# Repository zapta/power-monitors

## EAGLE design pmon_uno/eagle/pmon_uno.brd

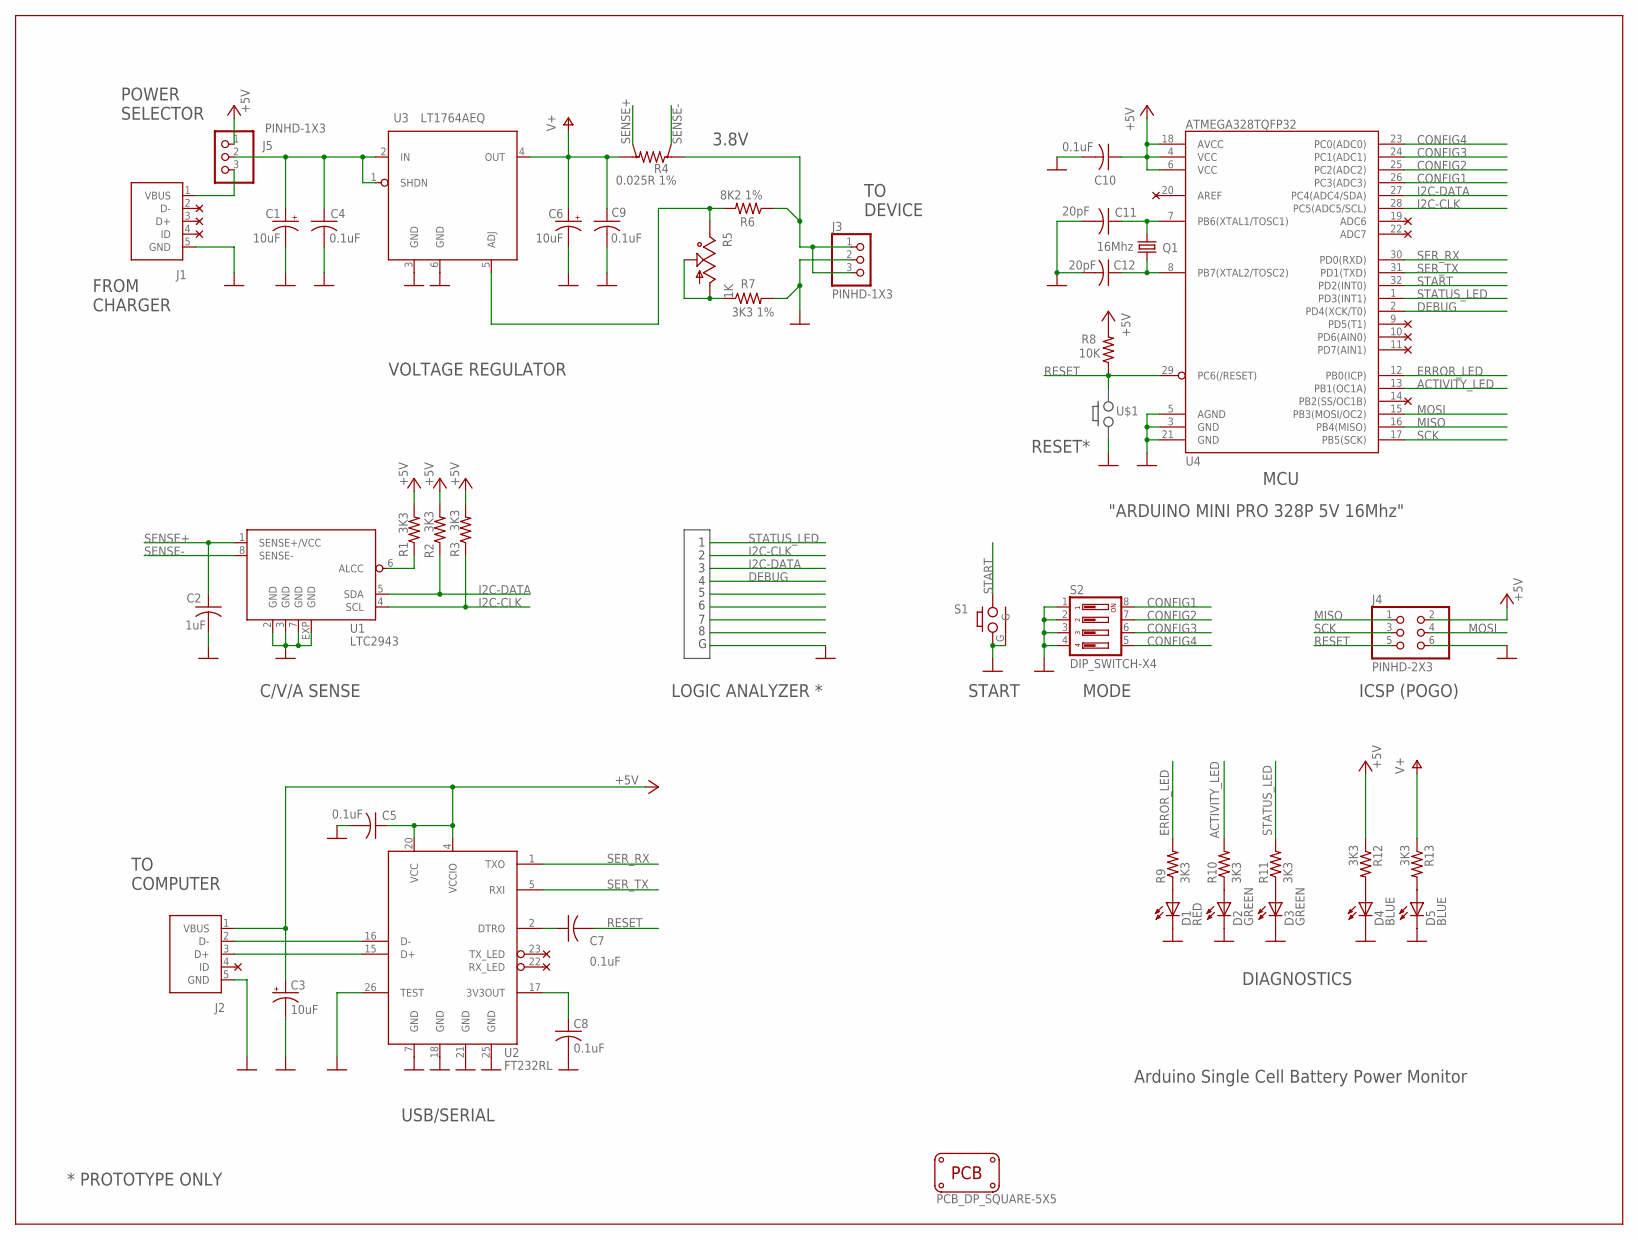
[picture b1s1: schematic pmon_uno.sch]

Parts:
C1, C3, C6: 10uF; A/3216-18R
C2: 1uF; C0603
C4, C5, C7, C8, C9, C10: 0.1uF; C0603
C11, C12: 20pF; C0603
D1: RED; 1206-LED
D2, D3: GREEN; 1206-LED
D4, D5: BLUE; 1206-LED
J1, J2: USB; USB-MICRO-ZX62RD-AB-5P8
J3, J5: PINHD-1X3; 1X03
J4: PINHD-2X3; 2X03
PCB1: PCB_DP_SQUARE-5X5; DP5050_V1
Q1: 16Mhz; CRYSTAL-CTS406
R1, R2, R3, R9, R10, R11, R12, R13: 3K3; R0603
R4: 0.025R 1%; KELVIN-6432
R5: 1K; TRIM-POT_SM-42/43A
R6: 8K2 1%; R0603
R7: 3K3 1%; R0603
R8: 10K; R0603
S1: PUSH_BUTTON_SHIELDED; TLE1105
S2: DIP_SWITCH-X4; DIP-SWITCH-X4
U1: LTC2943; DFN8-3X3
U2: FT232RL; SSOP28DB
U3: LT1764AEQ; TO263-5
U4: ATMEGA328TQFP32; TQFP32-08

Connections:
+5V: C3.+, C5.1, C10.1, J2.1 (VBUS), J4.2, J5.1, R1.2, R2.2, R3.2, R8.2, R12.1, U2.4 (VCCIO), U2.20 (VCC), U4.4 (VCC), U4.6 (VCC), U4.18 (AVCC)
ACTIVITY_LED: R10.2, U4.13 (PB1(OC1A))
CONFIG1: S2.8, U4.26 (PC3(ADC3))
CONFIG2: S2.7, U4.25 (PC2(ADC2))
CONFIG3: S2.6, U4.24 (PC1(ADC1))
CONFIG4: S2.5, U4.23 (PC0(ADC0))
DEBUG: U4.2 (PD4(XCK/T0))
ERROR_LED: R9.2, U4.12 (PB0(ICP))
GND: C1.-, C2.2, C3.-, C4.2, C5.2, C6.-, C8.2, C9.2, C10.2, C11.2, C12.2, D1.C, D2.C, D3.C, D4.C, D5.C, J1.5 (GND), J2.5 (GND), J3.2, J4.6, R7.2, S1.A (1), S1.G, S2.1, S2.2, S2.3, S2.4, U1.2 (GND), U1.3 (GND), U1.7 (GND), U1.EXP (GND), U2.7 (GND), U2.18 (GND), U2.21 (GND), U2.25 (GND), U2.26 (TEST), U3.3 (GND), U3.6 (GND), U4.3 (GND), U4.5 (AGND), U4.21 (GND)
I2C-CLK: R3.1, U1.4 (SCL), U4.28 (PC5(ADC5/SCL))
I2C-DATA: R2.1, U1.5 (SDA), U4.27 (PC4(ADC4/SDA))
MISO: J4.1, U4.16 (PB4(MISO))
MOSI: J4.4, U4.15 (PB3(MOSI/OC2))
unnamed: R1.1, U1.6 (ALCC)
unnamed: C11.1, Q1.1, U4.7 (PB6(XTAL1/TOSC1))
unnamed: D2.A, R10.1
unnamed: D1.A, R9.1
unnamed: J1.1 (VBUS), J5.3
unnamed: C12.1, Q1.3 (2), U4.8 (PB7(XTAL2/TOSC2))
unnamed: C1.+, C4.1, J5.2, U3.1 (SHDN), U3.2 (IN)
unnamed: J2.3 (D+), U2.15 (D+)
unnamed: C7.1, U2.2 (DTRO)
unnamed: D5.A, R13.2
unnamed: J2.2 (D-), U2.16 (D-)
unnamed: C8.1, U2.17 (3V3OUT)
unnamed: D4.A, R12.2
unnamed: R5.1, R5.2, R7.1
unnamed: R5.3, R6.2, U3.5 (ADJ)
unnamed: D3.A, R11.1
unnamed: J3.1, J3.3, R4.I1, R6.1
RESET: C7.2, J4.5, R8.1, U4.29 (PC6(/RESET))
SCK: J4.3, U4.17 (PB5(SCK))
SENSE+: C2.1, R4.V2, U1.1 (SENSE+/VCC)
SENSE-: R4.V1, U1.8 (SENSE-)
SER_RX: U2.1 (TXO), U4.30 (PD0(RXD))
SER_TX: U2.5 (RXI), U4.31 (PD1(TXD))
START: S1.B (2), U4.32 (PD2(INT0))
STATUS_LED: R11.2, U4.1 (PD3(INT1))
V+: C6.+, C9.1, R4.I2, R13.1, U3.4 (OUT)

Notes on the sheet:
USB/SERIAL
ICSP (POGO)
MCU
Arduino Single Cell Battery Power Monitor
DIAGNOSTICS
C/V/A SENSE
VOLTAGE REGULATOR
FROM CHARGER
LOGIC ANALYZER *
TO COMPUTER
TO DEVICE
MODE
3.8V
* PROTOTYPE ONLY
RESET*
"ARDUINO MINI PRO 328P 5V 16Mhz"
START
POWER SELECTOR

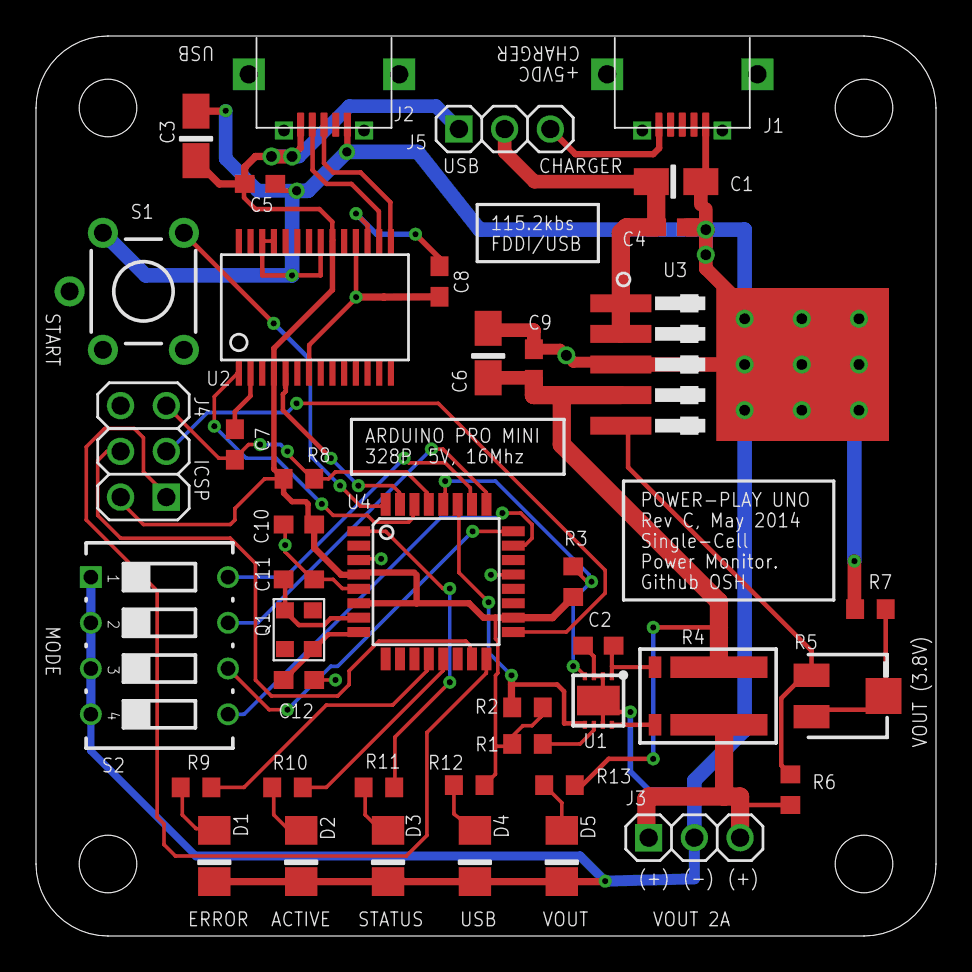
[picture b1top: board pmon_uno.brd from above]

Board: 2 copper layers, 50.0 x 50.0 mm, 43 parts (0 on the bottom side), 38 nets.

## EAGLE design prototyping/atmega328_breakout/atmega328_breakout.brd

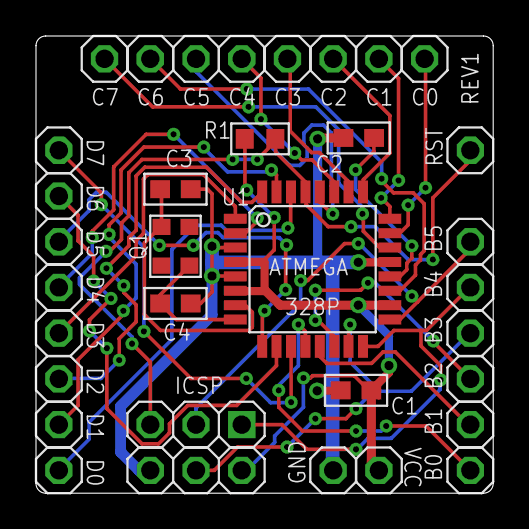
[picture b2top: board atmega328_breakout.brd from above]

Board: 2 copper layers, 25.4 x 25.4 mm, 33 parts (0 on the bottom side), 28 nets.

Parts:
C1, C2: 0.1uF; C0603
C3, C4: 20pF; C0603
GND: 1X01
J1: ICSP
PB0, PB1, PB2, PB3, PB4, PB5: 1X01
PC0, PC1, PC2, PC3, PC4, PC5, PC6, PC7: 1X01
PD0, PD1, PD2, PD3, PD4, PD5, PD6, PD7: 1X01
Q1: 16Mhz; CRYSTAL-CTS406
R1: 10K; R0603
RST: 1X01
U1: ATMEGA328TQFP32; TQFP32-08
VCC: 1X01

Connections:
AREF: C2.1, U1.20
GND: C1.2, C2.2, C3.2, C4.2, GND.1, J1.GND, U1.3, U1.5, U1.21
unnamed: C3.1, Q1.1, U1.7
unnamed: C4.1, Q1.3, U1.8
PB0: PB0.1, U1.12
PB1: PB1.1, U1.13
PB2: PB2.1, U1.14
PB3: J1.MOSI, PB3.1, U1.15
PB4: J1.MISO, PB4.1, U1.16
PB5: J1.SCK, PB5.1, U1.17
PC0: PC0.1, U1.23
PC1: PC1.1, U1.24
PC2: PC2.1, U1.25
PC3: PC3.1, U1.26
PC4: PC4.1, U1.27
PC5: PC5.1, U1.28
PC6: PC6.1, U1.19
PC7: PC7.1, U1.22
PD0: PD0.1, U1.30
PD1: PD1.1, U1.31
PD2: PD2.1, U1.32
PD3: PD3.1, U1.1
PD4: PD4.1, U1.2
PD5: PD5.1, U1.9
PD6: PD6.1, U1.10
PD7: PD7.1, U1.11
RESET: J1.RESET, R1.1, RST.1, U1.29
VCC: C1.1, J1.VCC, R1.2, U1.4, U1.6, U1.18, VCC.1
